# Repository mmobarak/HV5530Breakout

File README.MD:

# HV5530 Breakout Board

This is a breakout board for the [MicroChip HV 5530](https://ww1.microchip.com/downloads/aemDocuments/documents/OTH/ProductDocuments/DataSheets/20005851A.pdf) Serial to Parallel Converter.

The component is only available as an SMD part and it doesn't quite fit on a QFP44 footprint, so a custom breakout board is necessary for breadboard prototyping.

This project is a KiCad 8 import of the Eagle CAD project  developed by [Frederick L](https://hackaday.io/Fredovsky) as part of his [French Nixie Hackaday Project](https://hackaday.io/project/158949-french-nixie-clock).

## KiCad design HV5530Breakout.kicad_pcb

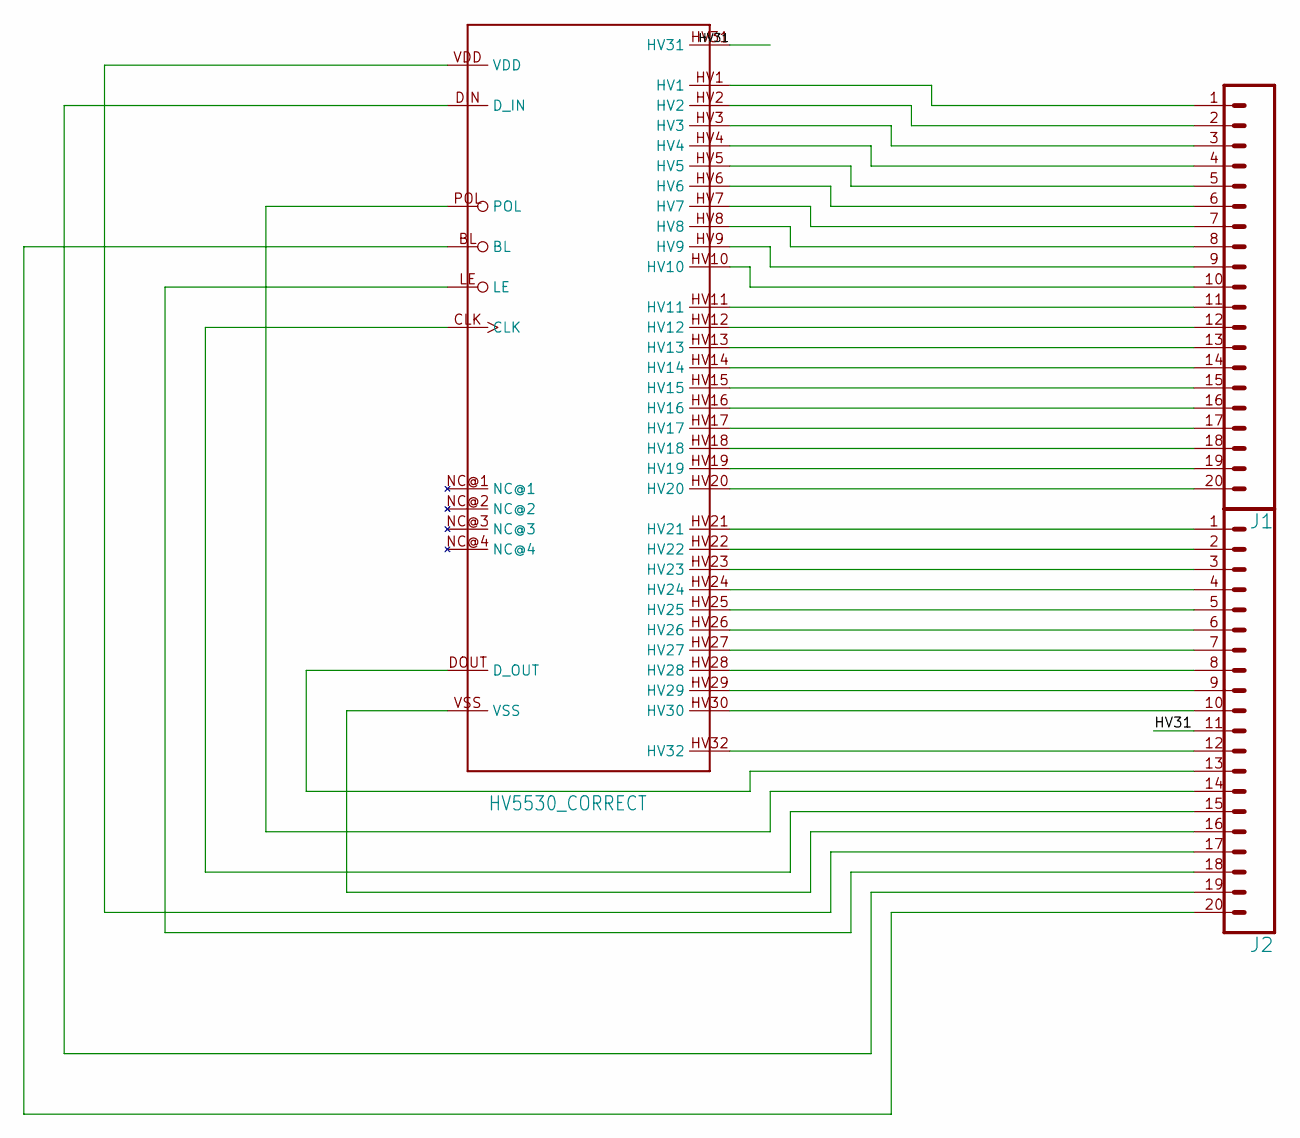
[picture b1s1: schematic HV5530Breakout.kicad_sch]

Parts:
J1, J2: CONN_20; 1X20
U$2: HV5530_CORRECT; 44_PQFP_CORRECTED

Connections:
BL: J2.20, U$2.BL
CLK: J2.15, U$2.CLK
D_IN: J2.19, U$2.DIN (D_IN)
D_OUT: J2.13, U$2.DOUT (D_OUT)
HV1: J1.1, U$2.HV1
HV2: J1.2, U$2.HV2
HV3: J1.3, U$2.HV3
HV4: J1.4, U$2.HV4
HV5: J1.5, U$2.HV5
HV6: J1.6, U$2.HV6
HV7: J1.7, U$2.HV7
HV8: J1.8, U$2.HV8
HV9: J1.9, U$2.HV9
HV10: J1.10, U$2.HV10
HV11: J1.11, U$2.HV11
HV12: J1.12, U$2.HV12
HV13: J1.13, U$2.HV13
HV14: J1.14, U$2.HV14
HV15: J1.15, U$2.HV15
HV16: J1.16, U$2.HV16
HV17: J1.17, U$2.HV17
HV18: J1.18, U$2.HV18
HV19: J1.19, U$2.HV19
HV20: J1.20, U$2.HV20
HV21: J2.1, U$2.HV21
HV22: J2.2, U$2.HV22
HV23: J2.3, U$2.HV23
HV24: J2.4, U$2.HV24
HV25: J2.5, U$2.HV25
HV26: J2.6, U$2.HV26
HV27: J2.7, U$2.HV27
HV28: J2.8, U$2.HV28
HV29: J2.9, U$2.HV29
HV30: J2.10, U$2.HV30
HV31: J2.11, U$2.HV31
HV32: J2.12, U$2.HV32
LE: J2.18, U$2.LE
POL: J2.14, U$2.POL
VDD: J2.17, U$2.VDD
VSS: J2.16, U$2.VSS

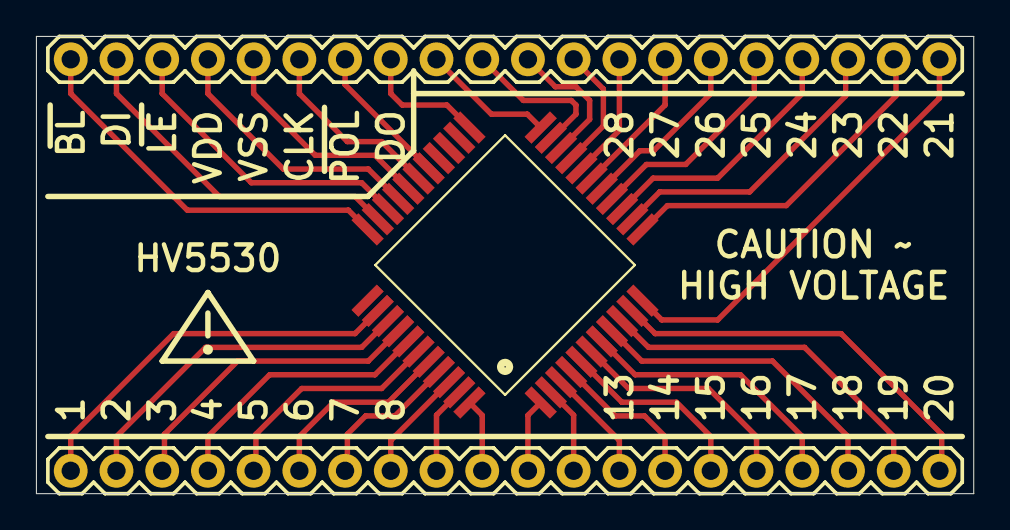
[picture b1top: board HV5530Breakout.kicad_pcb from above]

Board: 2 copper layers, 52.1 x 25.4 mm, 3 parts (0 on the bottom side), 40 nets.

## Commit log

2024-11-19 inital import from EAGLE project
2024-11-19 Markdown Lint should ignore files without MD extension
2024-11-19 README
